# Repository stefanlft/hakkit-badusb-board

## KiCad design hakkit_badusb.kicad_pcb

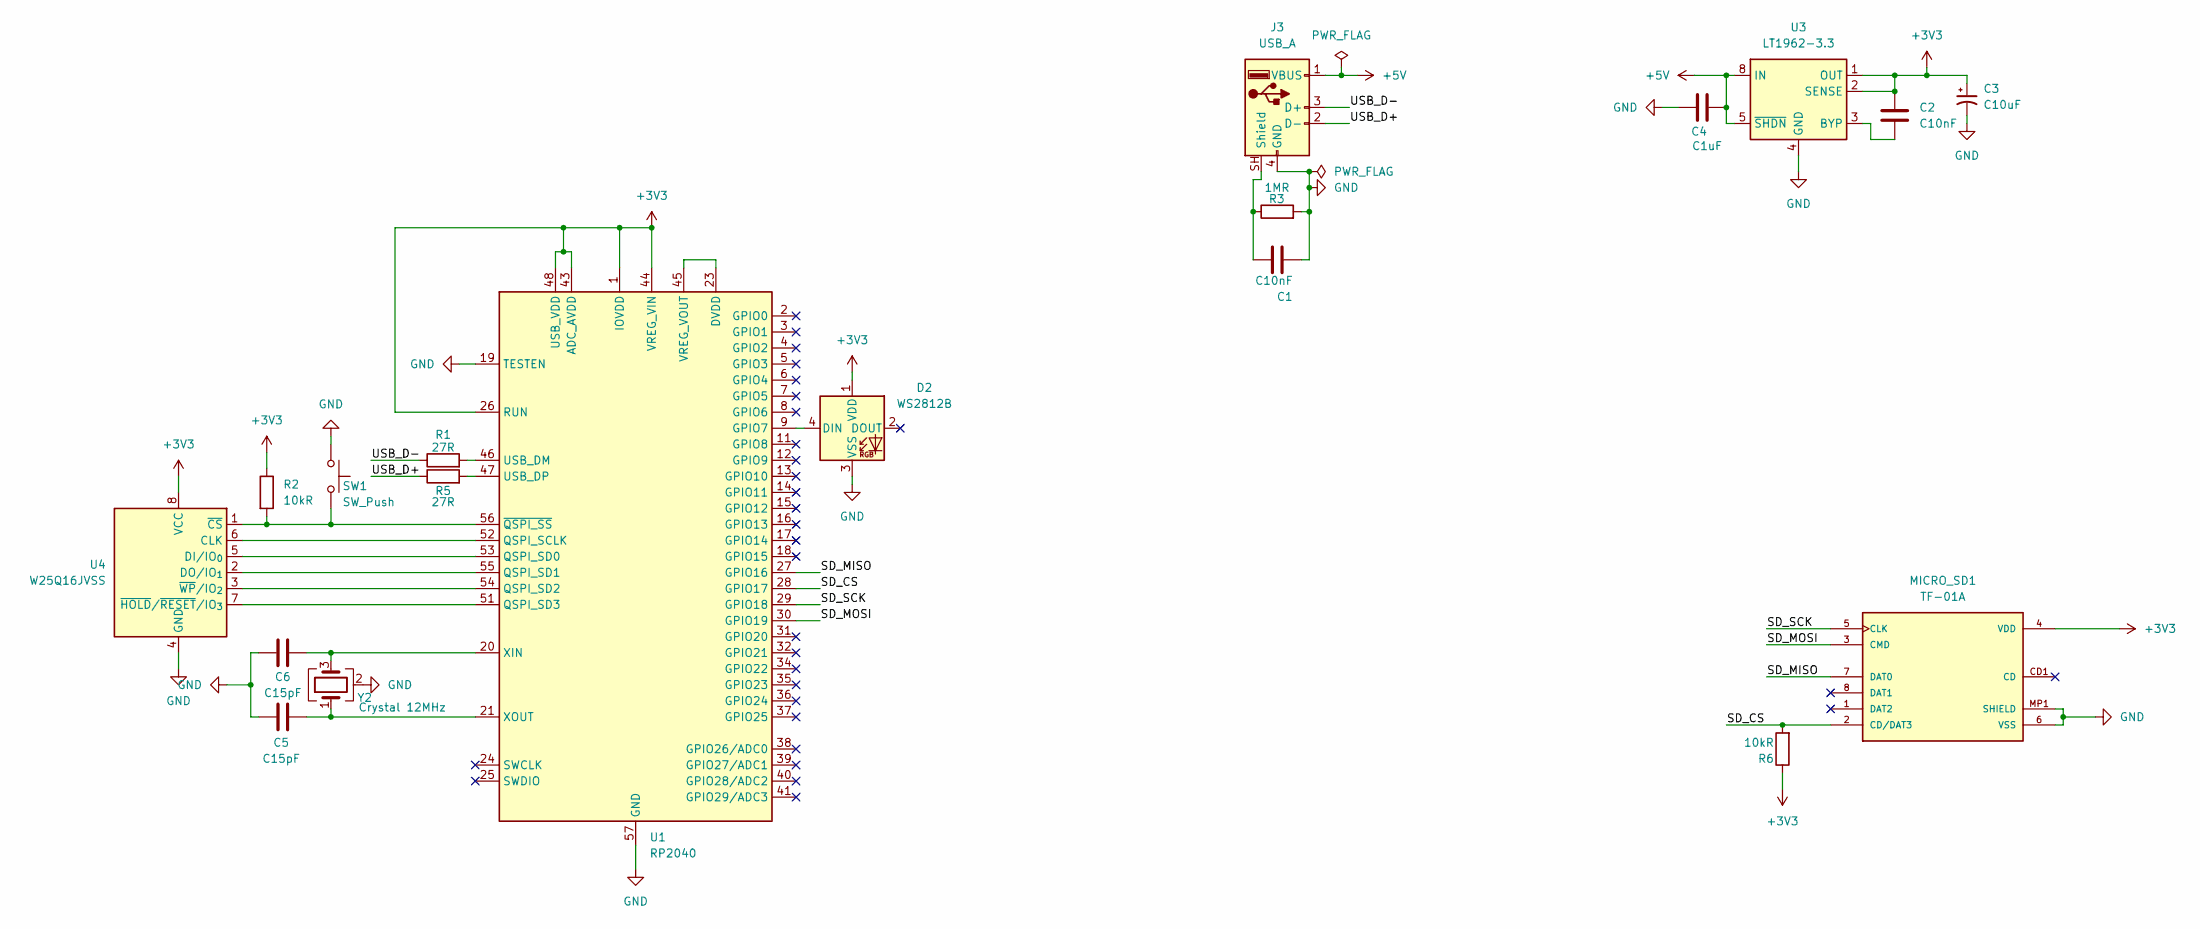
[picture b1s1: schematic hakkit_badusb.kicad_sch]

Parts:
C1, C2: C10nF; C_0603_1608Metric
C3: C10uF; CP_Elec_5x3
C4: C1uF; C_0603_1608Metric
C5, C6: C15pF; C_0603_1608Metric
D2: WS2812B; LED_WS2812B_PLCC4_5.0x5.0mm_P3.2mm
J3: USB_A; USB_A_Connfly_DS1098_Horizontal
MICRO_SD1: TF-01A
R1, R5: 27R; R_0603_1608Metric
R2, R6: 10kR; R_0603_1608Metric
R3: 1MR; R_0603_1608Metric
SW1: SW_Push; SW_Push_1P1T_NO_CK_KMR2
U1: RP2040; QFN-56-1EP_7x7mm_P0.4mm_EP3.2x3.2mm
U3: LT1962-3.3; MSOP-8_3x3mm_P0.65mm
U4: W25Q16JVSS; SOIC-8_5.3x5.3mm_P1.27mm
Y2: Crystal 12MHz; Crystal_SMD_3225-4Pin_3.2x2.5mm

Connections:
+3V3: C2.1, C3.1, D2.1 (VDD), MICRO_SD1.4 (VDD), R2.1, R6.1, U1.1 (IOVDD), U1.10 (IOVDD), U1.22 (IOVDD), U1.26 (RUN), U1.33 (IOVDD), U1.42 (IOVDD), U1.43 (ADC_AVDD), U1.44 (VREG_VIN), U1.48 (USB_VDD), U1.49 (IOVDD), U3.1 (OUT), U3.2 (SENSE), U4.8 (VCC)
+5V: C4.1, J3.1 (VBUS), U3.5 (~SHDN), U3.8 (IN)
/SD_CS: MICRO_SD1.2 (CD/DAT3), R6.2, U1.28 (GPIO17)
/SD_MISO: MICRO_SD1.7 (DAT0), U1.27 (GPIO16)
/SD_MOSI: MICRO_SD1.3 (CMD), U1.30 (GPIO19)
/SD_SCK: MICRO_SD1.5 (CLK), U1.29 (GPIO18)
/USB_D+: J3.2 (D-), R5.1
/USB_D-: J3.3 (D+), R1.1
GND: C1.2, C3.2, C4.2, C5.2, C6.2, D2.3 (VSS), J3.4 (GND), MICRO_SD1.6 (VSS), MICRO_SD1.MP1 (SHIELD), MICRO_SD1.MP2 (SHIELD), MICRO_SD1.MP3 (SHIELD), MICRO_SD1.MP4 (SHIELD), R3.2, SW1.1, U1.19 (TESTEN), U1.57 (GND), U3.4 (GND), U4.4 (GND), Y2.2 (G), Y2.4 (G)
unnamed: D2.4 (DIN), U1.9 (GPIO7)
unnamed: C1.1, J3.SH (Shield), R3.1
unnamed: U1.52 (QSPI_SCLK), U4.6 (CLK)
unnamed: U1.53 (QSPI_SD0), U4.5 (DI/IO_{0})
unnamed: U1.55 (QSPI_SD1), U4.2 (DO/IO_{1})
unnamed: U1.54 (QSPI_SD2), U4.3 (~WP/IO_{2})
unnamed: U1.51 (QSPI_SD3), U4.7 (~HOLD/~RESET/IO_{3})
unnamed: R1.2, U1.46 (USB_DM)
unnamed: R5.2, U1.47 (USB_DP)
unnamed: U1.23 (DVDD), U1.45 (VREG_VOUT), U1.50 (DVDD)
unnamed: C6.1, U1.20 (XIN), Y2.3
unnamed: C5.1, U1.21 (XOUT), Y2.1
unnamed: R2.2, SW1.2, U1.56 (~QSPI_SS), U4.1 (~CS)
unnamed: C2.2, U3.3 (BYP)

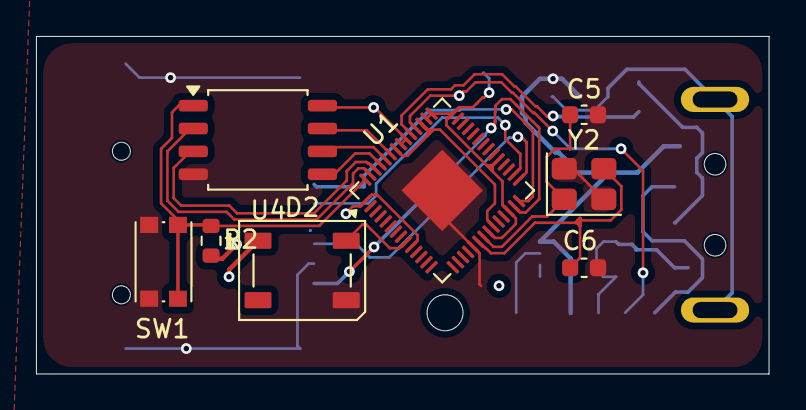
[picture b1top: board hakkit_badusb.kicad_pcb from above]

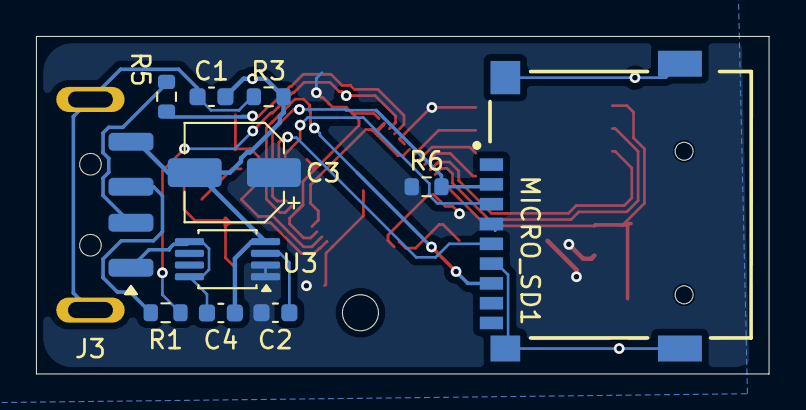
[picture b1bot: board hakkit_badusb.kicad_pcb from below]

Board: 2 copper layers, 40.7 x 18.8 mm, 19 parts (11 on the bottom side), 23 nets.
